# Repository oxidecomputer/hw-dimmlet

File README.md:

# hw-dimmlet

Breaks out I2C connections to 2x DIMM sockets to a PMOD i2c interface for SPD work.
Works well with gimletlet

# Status
Rev1 required MCNs as documented. CAD was updated to resolve these
issues but new CAD was not actually built since the reworked rev1s
served their purpose

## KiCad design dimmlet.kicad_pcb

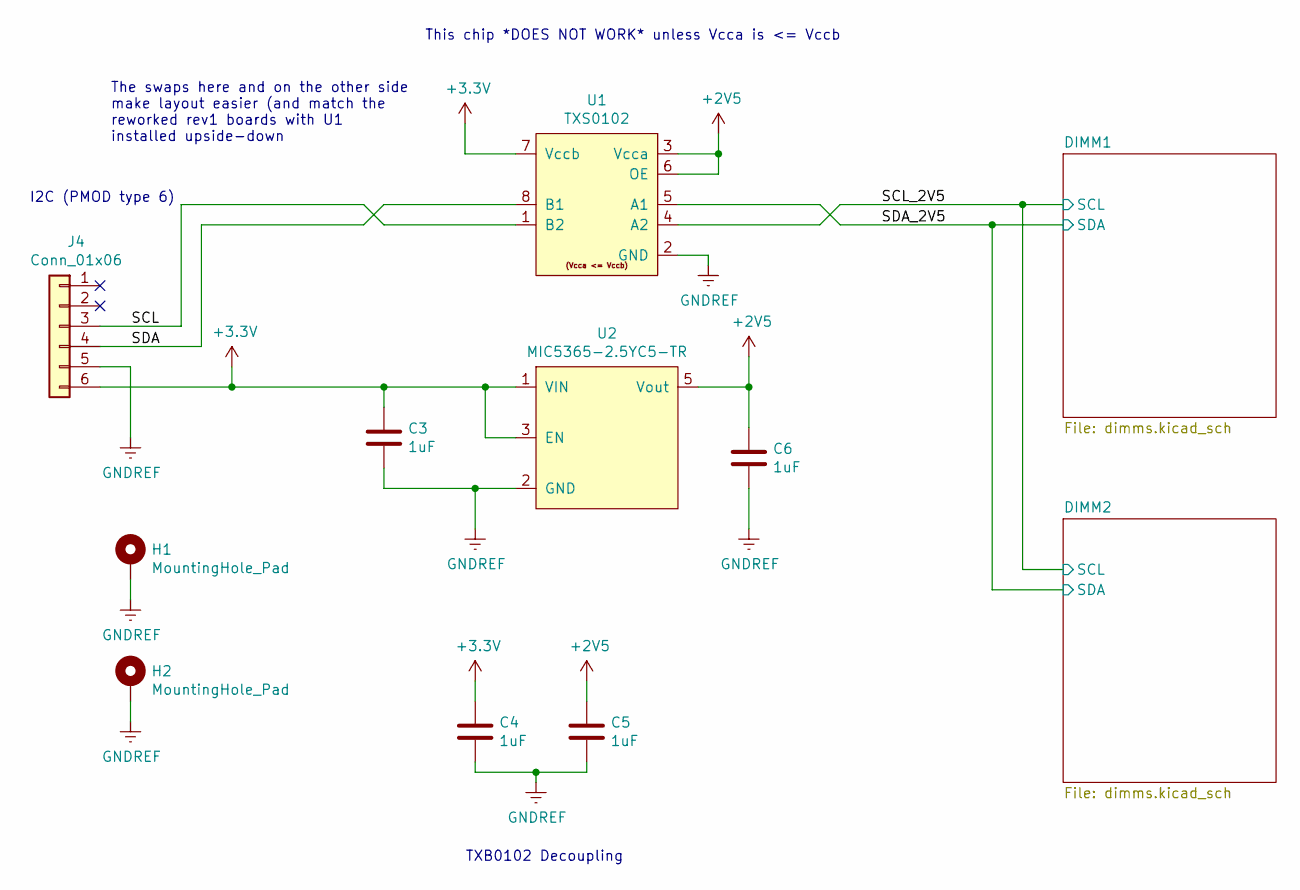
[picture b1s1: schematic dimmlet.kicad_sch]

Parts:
C3, C4, C5, C6: 1uF; C_0402_1005Metric_Pad0.74x0.62mm_HandSolder
H1, H2: MountingHole_Pad; MountingHole_2.2mm_M2_DIN965_Pad
J4: Conn_01x06; PMOD_6pin_peripheral_horizontal
U1: ‎TXS0102; VSSOP-8_2.4x2.1mm_P0.5mm
U2: ‎MIC5365-2.5YC5-TR; SOT-353_SC-70-5

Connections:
+2V5: C5.1, C6.1, U1.3 (Vcca), U1.6 (OE), U2.5 (Vout); also elsewhere on the board
+3V3: C3.1, C4.1, J4.6, U1.7 (Vccb), U2.1 (VIN), U2.3 (EN)
/SCL: J4.3, U1.1 (B2)
/SCL_2V5: U1.4 (A2); also elsewhere on the board
/SDA: J4.4, U1.8 (B1)
/SDA_2V5: U1.5 (A1); also elsewhere on the board
GNDREF: C3.2, C4.2, C5.2, C6.2, H1.1, H2.1, J4.5, U1.2 (GND), U2.2 (GND); also elsewhere on the board

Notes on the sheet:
The swaps here and on the other side make layout easier (and match the reworked rev1 boards with U1 installed upside-down
I2C (PMOD type 6)
TXB0102 Decoupling
This chip *DOES NOT WORK* unless Vcca is <= Vccb

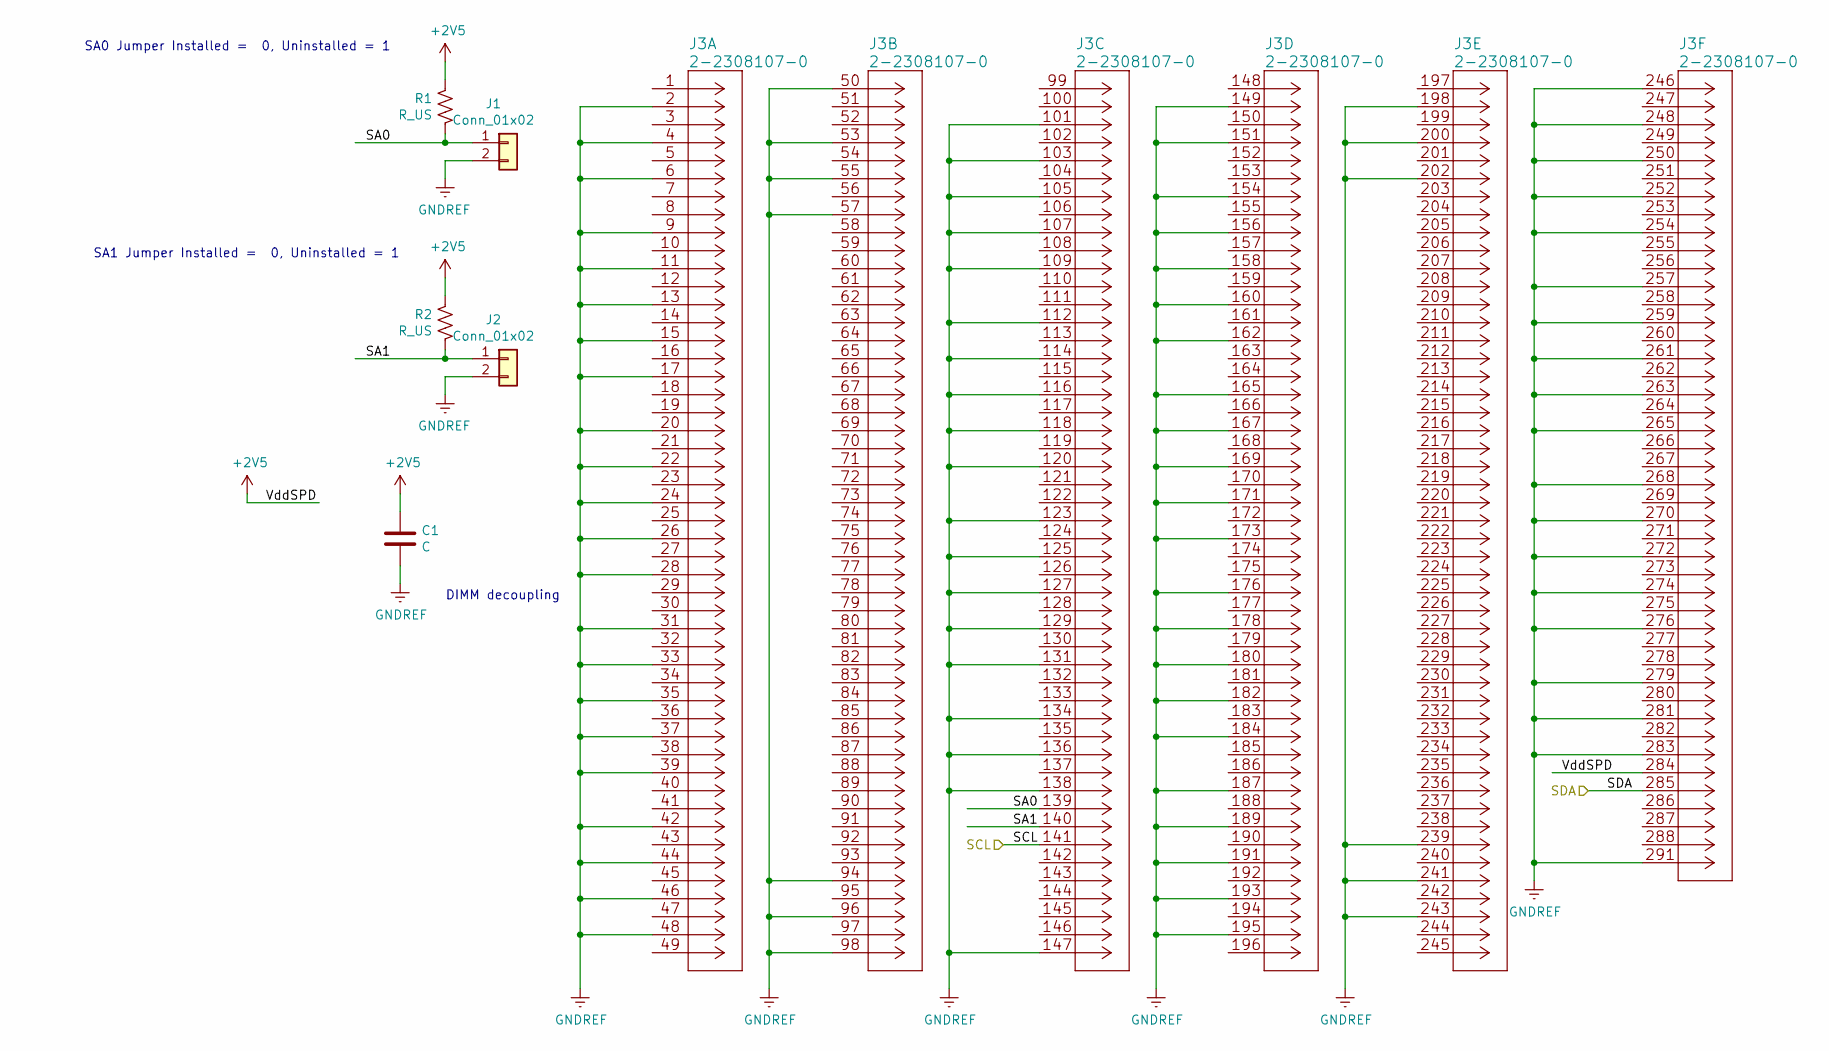
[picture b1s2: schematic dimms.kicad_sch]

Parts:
C1: C; C_0402_1005Metric_Pad0.74x0.62mm_HandSolder
J1, J2: Conn_01x02; PinHeader_1x02_P2.54mm_Vertical
J3: 2-2308107-0
R1, R2: R_US; R_0402_1005Metric_Pad0.72x0.64mm_HandSolder

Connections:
+2V5: C1.1, J3.284, R1.1, R2.1; also elsewhere on the board
/DIMM1/SA0: J1.1, J3.139, R1.2
/DIMM1/SA1: J2.1, J3.140, R2.2
/SCL_2V5: J3.141; also elsewhere on the board
/SDA_2V5: J3.285; also elsewhere on the board
GNDREF: C1.2, J1.2, J2.2, J3.2, J3.4, J3.6, J3.9, J3.11, J3.13, J3.15, J3.17, J3.20, J3.22, J3.24, J3.26, J3.28, J3.31, J3.33, J3.35, J3.37, J3.39, J3.42, J3.44, J3.46, J3.48, J3.50, J3.53, J3.55, J3.57, J3.94, J3.96, J3.98, J3.101, J3.103, J3.105, J3.107, J3.109, J3.112, J3.114, J3.116, J3.118, J3.120, J3.123, J3.125, J3.127, J3.129, J3.131, J3.134, J3.136, J3.138, J3.147, J3.149, J3.151, J3.154, J3.156, J3.158, J3.160, J3.162, J3.165, J3.167, J3.169, J3.171, J3.173, J3.176, J3.178, J3.180, J3.182, J3.184, J3.187, J3.189, J3.191, J3.193, J3.195, J3.198, J3.200, J3.202, J3.239, J3.241, J3.243, J3.246, J3.248, J3.250, J3.252, J3.254, J3.257, J3.259, J3.261, J3.263, J3.265, J3.268, J3.270, J3.272, J3.274, J3.276, J3.279, J3.281, J3.283, J3.291; also elsewhere on the board

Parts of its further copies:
C2: C; C_0402_1005Metric_Pad0.74x0.62mm_HandSolder
J5, J6: Conn_01x02; PinHeader_1x02_P2.54mm_Vertical
J7: 2-2308107-0
R3, R4: R_US; R_0402_1005Metric_Pad0.72x0.64mm_HandSolder

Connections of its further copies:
+2V5: C2.1, J7.284, R3.1, R4.1; also elsewhere on the board
/DIMM2/SA0: J5.1, J7.139, R3.2
/DIMM2/SA1: J6.1, J7.140, R4.2
/SCL_2V5: J7.141; also elsewhere on the board
/SDA_2V5: J7.285; also elsewhere on the board
GNDREF: C2.2, J5.2, J6.2, J7.2, J7.4, J7.6, J7.9, J7.11, J7.13, J7.15, J7.17, J7.20, J7.22, J7.24, J7.26, J7.28, J7.31, J7.33, J7.35, J7.37, J7.39, J7.42, J7.44, J7.46, J7.48, J7.50, J7.53, J7.55, J7.57, J7.94, J7.96, J7.98, J7.101, J7.103, J7.105, J7.107, J7.109, J7.112, J7.114, J7.116, J7.118, J7.120, J7.123, J7.125, J7.127, J7.129, J7.131, J7.134, J7.136, J7.138, J7.147, J7.149, J7.151, J7.154, J7.156, J7.158, J7.160, J7.162, J7.165, J7.167, J7.169, J7.171, J7.173, J7.176, J7.178, J7.180, J7.182, J7.184, J7.187, J7.189, J7.191, J7.193, J7.195, J7.198, J7.200, J7.202, J7.239, J7.241, J7.243, J7.246, J7.248, J7.250, J7.252, J7.254, J7.257, J7.259, J7.261, J7.263, J7.265, J7.268, J7.270, J7.272, J7.274, J7.276, J7.279, J7.281, J7.283, J7.291; also elsewhere on the board

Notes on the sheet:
DIMM decoupling
SA0 Jumper Installed = 0, Uninstalled = 1
SA1 Jumper Installed = 0, Uninstalled = 1

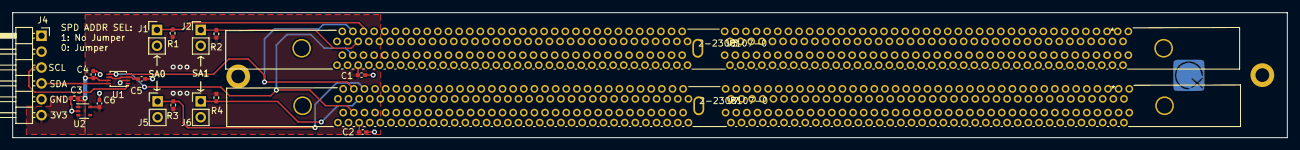
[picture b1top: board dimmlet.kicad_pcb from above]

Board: 2 copper layers, 204.0 x 20.0 mm, 21 parts (0 on the bottom side), 11 nets.

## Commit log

2023-02-24 Initial commit after restructuring

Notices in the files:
parts and their libraries:
Copyright 2021 Accelerated Designs. All rights reserved.
